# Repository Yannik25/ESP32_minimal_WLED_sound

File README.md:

# ESP32_minimal_WLED_sound

 Either install WLED and configure Digital LEDs on GPIO 2 and 4 with following functions:
 - 2 channels for Digital LEDs
 - 1 mosfet switch output
 - sound reactive with microphone
 
 or install ESPHome to have full support of following:
 - 2 channels for Digital LEDs
 - 1 mosfet switch output
 - INA226 current sensing

# ESPHome ESP32 Sound Module WebInstaller

ESPHome Configuration:

It includes a GitHub workflow that will automatically build the configuration(s) and then deploys a simple 
website via GitHub pages that utilises [ESP Web Tools](https://esphome.github.io/esp-web-tools/) for users to 
easily install your project onto their device.

## Instructions
Open: [https://yannik25.github.io/ESP32_minimal_WLED_sound/](https://yannik25.github.io/ESP32_minimal_WLED_sound/) and follow instructions.

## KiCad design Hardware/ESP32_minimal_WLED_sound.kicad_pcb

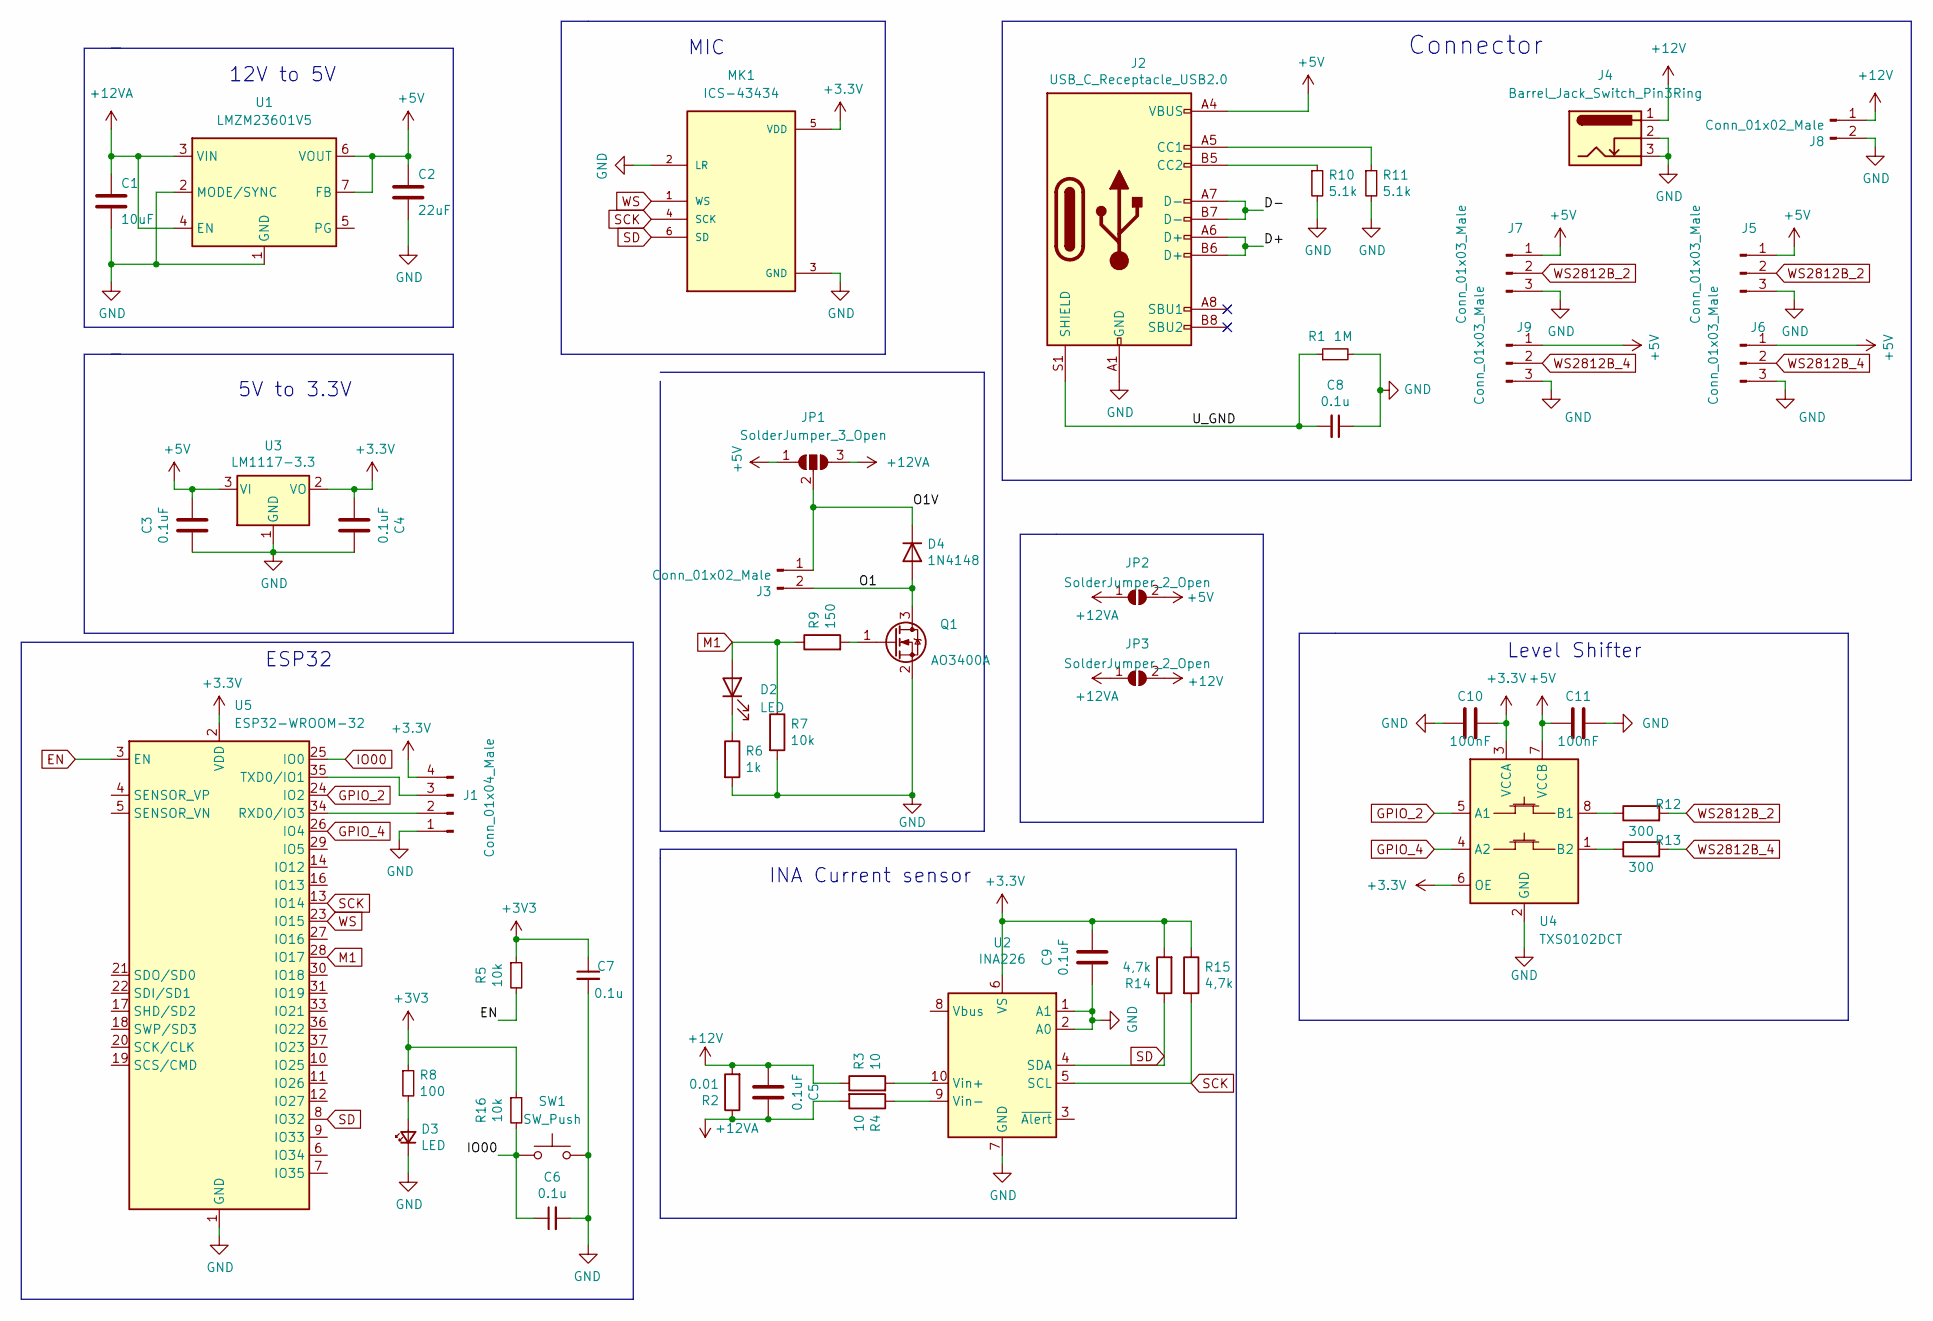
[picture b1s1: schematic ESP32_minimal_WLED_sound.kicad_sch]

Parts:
C1: 10uF; C_0603_1608Metric
C2: 22uF; C_0805_2012Metric
C3, C4, C9: 0.1uF; C_0805_2012Metric
C5: 0.1uF; C_0603_1608Metric
C6, C7, C8: 0.1u; C_0603_1608Metric; LCSC C14663
C10, C11: 100nF; C_0603_1608Metric
D2: LED; LED_0603_1608Metric
D3: LED; LED_0603_1608Metric; LCSC C205445
D4: 1N4148; D_1206_3216Metric
J1: Conn_01x04_Male; PinHeader_1x04_P2.54mm_Vertical
J2: USB_C_Receptacle_USB2.0; USB_C_Receptacle_HRO_TYPE-C-31-M-12; LCSC C165948
J3, J8: Conn_01x02_Male; TerminalBlock_Phoenix_MKDS-1,5-2-5.08_1x02_P5.08mm_Horizont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
J4: Barrel_Jack_Switch_Pin3Ring; BarrelJack_GCT_DCJ200-10-A_Horizontal
J5, J6: Conn_01x03_Male; JST_EH_B3B-EH-A_1x03_P2.50mm_Vertical
J7, J9: Conn_01x03_Male; PinHeader_1x03_P2.54mm_Vertical
JP1: SolderJumper_3_Open; SolderJumper-3_P1.3mm_Open_Pad1.0x1.5mm
JP2, JP3: SolderJumper_2_Open; SolderJumper-2_P1.3mm_Open_Pad1.0x1.5mm
MK1: ICS-43434; MIC_ICS-43434
Q1: AO3400A; SOT-23
R1: 1M; R_0603_1608Metric; LCSC C163928
R2: 0.01; R_0805_2012Metric
R3, R4: 10; R_0603_1608Metric
R5, R16: 10k; R_0603_1608Metric; LCSC C99198
R6: 1k; R_0603_1608Metric
R7: 10k; R_0603_1608Metric
R8: 100; R_0603_1608Metric; LCSC C22775
R9: 150; R_0603_1608Metric
R10, R11: 5.1k; R_0603_1608Metric; LCSC C163928
R12, R13: 300; R_0603_1608Metric
R14, R15: 4,7k; R_0603_1608Metric
SW1: SW_Push; SW_Push_SPST_NO_Alps_SKRK
U1: LMZM23601V5; Texas_SIL0010A_MicroSiP-10-1EP_3.8x3mm_P0.6mm_EP0.7x2.9mm_T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
U2: INA226; VSSOP-10_3x3mm_P0.5mm
U3: LM1117-3.3; SOT-223
U4: TXS0102DCT; SSOP-8_2.95x2.8mm_P0.65mm
U5: ESP32-WROOM-32

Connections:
+5V: C2.1, C3.1, C11.1, J2.A4 (VBUS), J2.A9 (VBUS), J2.B4 (VBUS), J2.B9 (VBUS), J5.1, J6.1, J7.1, J9.1, JP1.1 (A), JP2.2 (B), U1.6 (VOUT), U1.7 (FB), U3.3 (VI), U4.7 (VCCB)
+12V: C5.2, J4.1, J8.1, JP3.2 (B), R2.2, R3.1
+12VA: C1.1, C5.1, JP1.3 (B), JP2.1 (A), JP3.1 (A), R2.1, R4.2, U1.3 (VIN), U1.4 (EN)
/D+: J2.A6 (D+), J2.B6 (D+)
/D-: J2.A7 (D-), J2.B7 (D-)
/O1: D4.2 (A), J3.2, Q1.3 (D)
/O1V: D4.1 (K), J3.1, JP1.2 (C)
/U_GND: C8.2, J2.S1 (SHIELD), R1.1
EN: R5.2, U5.3 (EN)
GND: C1.2, C2.2, C3.2, C4.1, C6.2, C7.2, C8.1, C9.2, C10.1, C11.2, D3.1 (K), J1.1, J2.A1 (GND), J2.A12 (GND), J2.B1 (GND), J2.B12 (GND), J4.2, J4.3, J5.3, J6.3, J7.3, J8.2, J9.3, MK1.2 (LR), MK1.3 (GND), Q1.2 (S), R1.2, R6.2, R7.2, R10.2, R11.2, SW1.2, U1.1 (GND), U1.2 (MODE/SYNC), U1.11 (GND), U2.1 (A1), U2.2 (A0), U2.7 (GND), U3.1 (GND), U4.2 (GND), U5.1 (GND), U5.15 (GND), U5.38 (GND), U5.39 (GND)
GPIO_2: U4.5 (A1), U5.24 (IO2)
GPIO_4: U4.4 (A2), U5.26 (IO4)
IO00: C6.1, R16.2, SW1.1, U5.25 (IO0)
M1: D2.2 (A), R7.1, R9.1, U5.28 (IO17)
unnamed: D2.1 (K), R6.1
unnamed: D3.2 (A), R8.2
unnamed: J1.2, U5.34 (RXD0/IO3)
unnamed: J1.3, U5.35 (TXD0/IO1)
unnamed: J2.A5 (CC1), R11.1
unnamed: J2.B5 (CC2), R10.1
unnamed: Q1.1 (G), R9.2
unnamed: R3.2, U2.10 (Vin+)
unnamed: R4.1, U2.9 (Vin-)
unnamed: R12.1, U4.8 (B1)
unnamed: R13.1, U4.1 (B2)
SCK: MK1.4 (SCK), R15.2, U2.5 (SCL), U5.13 (IO14)
SD: MK1.6 (SD), R14.1, U2.4 (SDA), U5.8 (IO32)
WS: MK1.1 (WS), U5.23 (IO15)
WS2812B_2: J5.2, J7.2, R12.2
WS2812B_4: J6.2, J9.2, R13.2

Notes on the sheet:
MIC
Level Shifter
ESP32
Connector
12V to 5V
5V to 3.3V
INA Current sensor

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
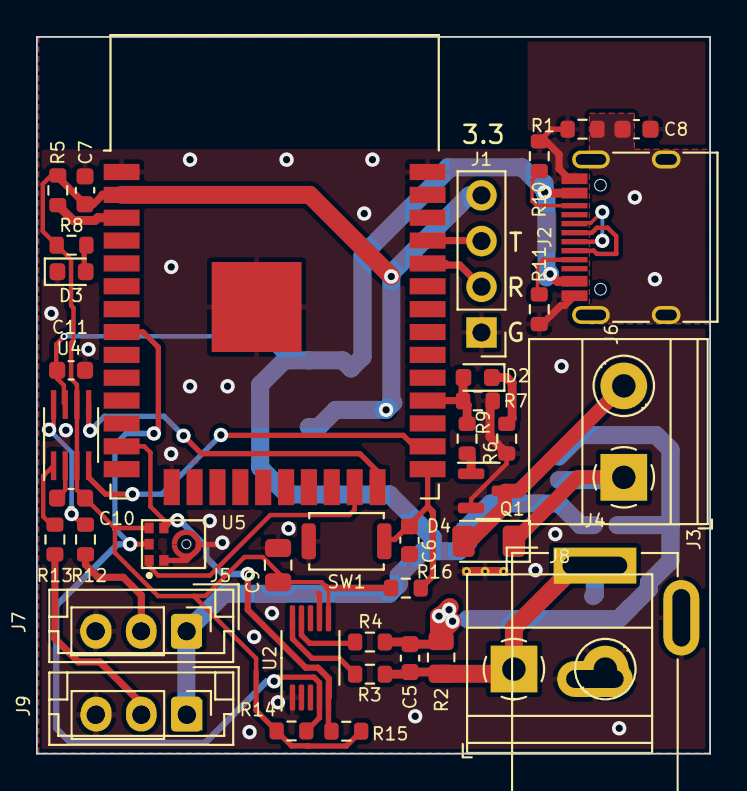
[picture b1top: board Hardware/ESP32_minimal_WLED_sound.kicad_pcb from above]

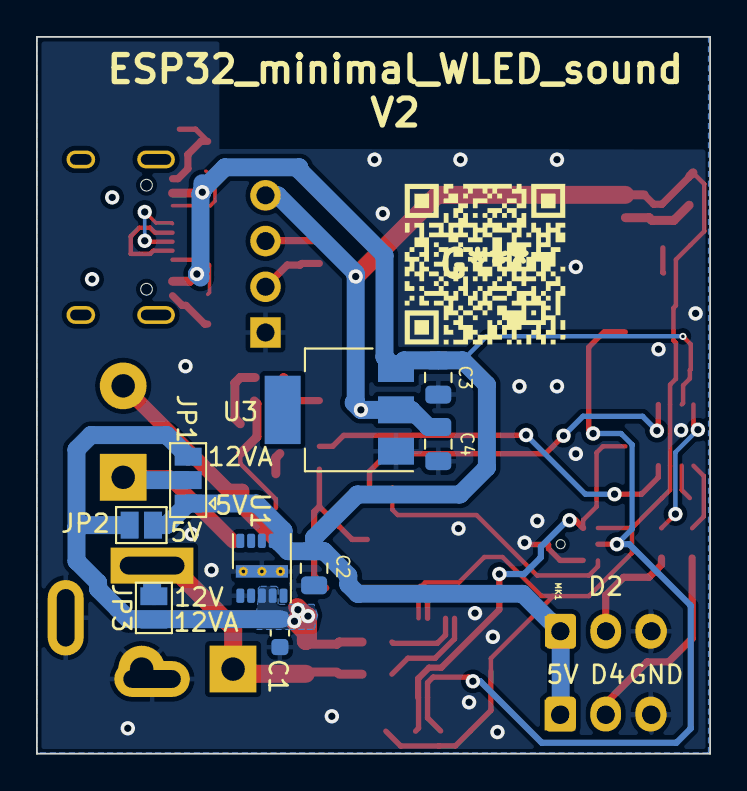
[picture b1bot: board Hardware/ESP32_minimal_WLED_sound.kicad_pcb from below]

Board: 2 copper layers, 37.4 x 39.8 mm, 50 parts (9 on the bottom side), 31 nets.

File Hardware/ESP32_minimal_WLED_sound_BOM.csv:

Comment,Designator,Footprint,LCSC
100nF,C1 C2 C3 C4 C9,Capacitor_SMD:C_0805_2012Metric,
100nF,C5 C6 C7 C8 C10 C11,Capacitor_SMD:C_0603_1608Metric,
LED,D2 D3,LED_SMD:LED_0603_1608Metric,
1N4148,D4,Diode_SMD:D_1206_3216Metric,
USB_C_Receptacle_USB2.0,J2,Connector_USB:USB_C_Receptacle_HRO_TYPE-C-31-M-12,C165948
ICS-43434,MK1,ICS-43434:MIC_ICS-43434,
AO3400A,Q1,Package_TO_SOT_SMD:SOT-23,
1M,R1,Resistor_SMD:R_0603_1608Metric,C163928
5.1k,R10 R11,Resistor_SMD:R_0603_1608Metric,C163928
300,R12 R13,Resistor_SMD:R_0603_1608Metric,
4,7k,R14 R15,Resistor_SMD:R_0603_1608Metric,
0.01,R2,Resistor_SMD:R_0805_2012Metric,
10,R3 R4,Resistor_SMD:R_0603_1608Metric,
10k,R5 R7,Resistor_SMD:R_0603_1608Metric,C99198
1k,R6,Resistor_SMD:R_0603_1608Metric,
100,R8,Resistor_SMD:R_0603_1608Metric,C22775
150,R9,Resistor_SMD:R_0603_1608Metric,
Boot,SW2,Button_Switch_SMD:SW_SPST_B3U-1000P-B,C115357
LM1117-5,U1,Package_TO_SOT_SMD:SOT-223,
INA226,U2,Package_SO:VSSOP-10_3x3mm_P0.5mm,
LM1117-3.3,U3,Package_TO_SOT_SMD:SOT-223,
TXS0102DCT,U4,Package_SO:SSOP-8_2.95x2.8mm_P0.65mm,
ESP32-WROOM-32,U5,RF_Module:ESP32-WROOM-32,

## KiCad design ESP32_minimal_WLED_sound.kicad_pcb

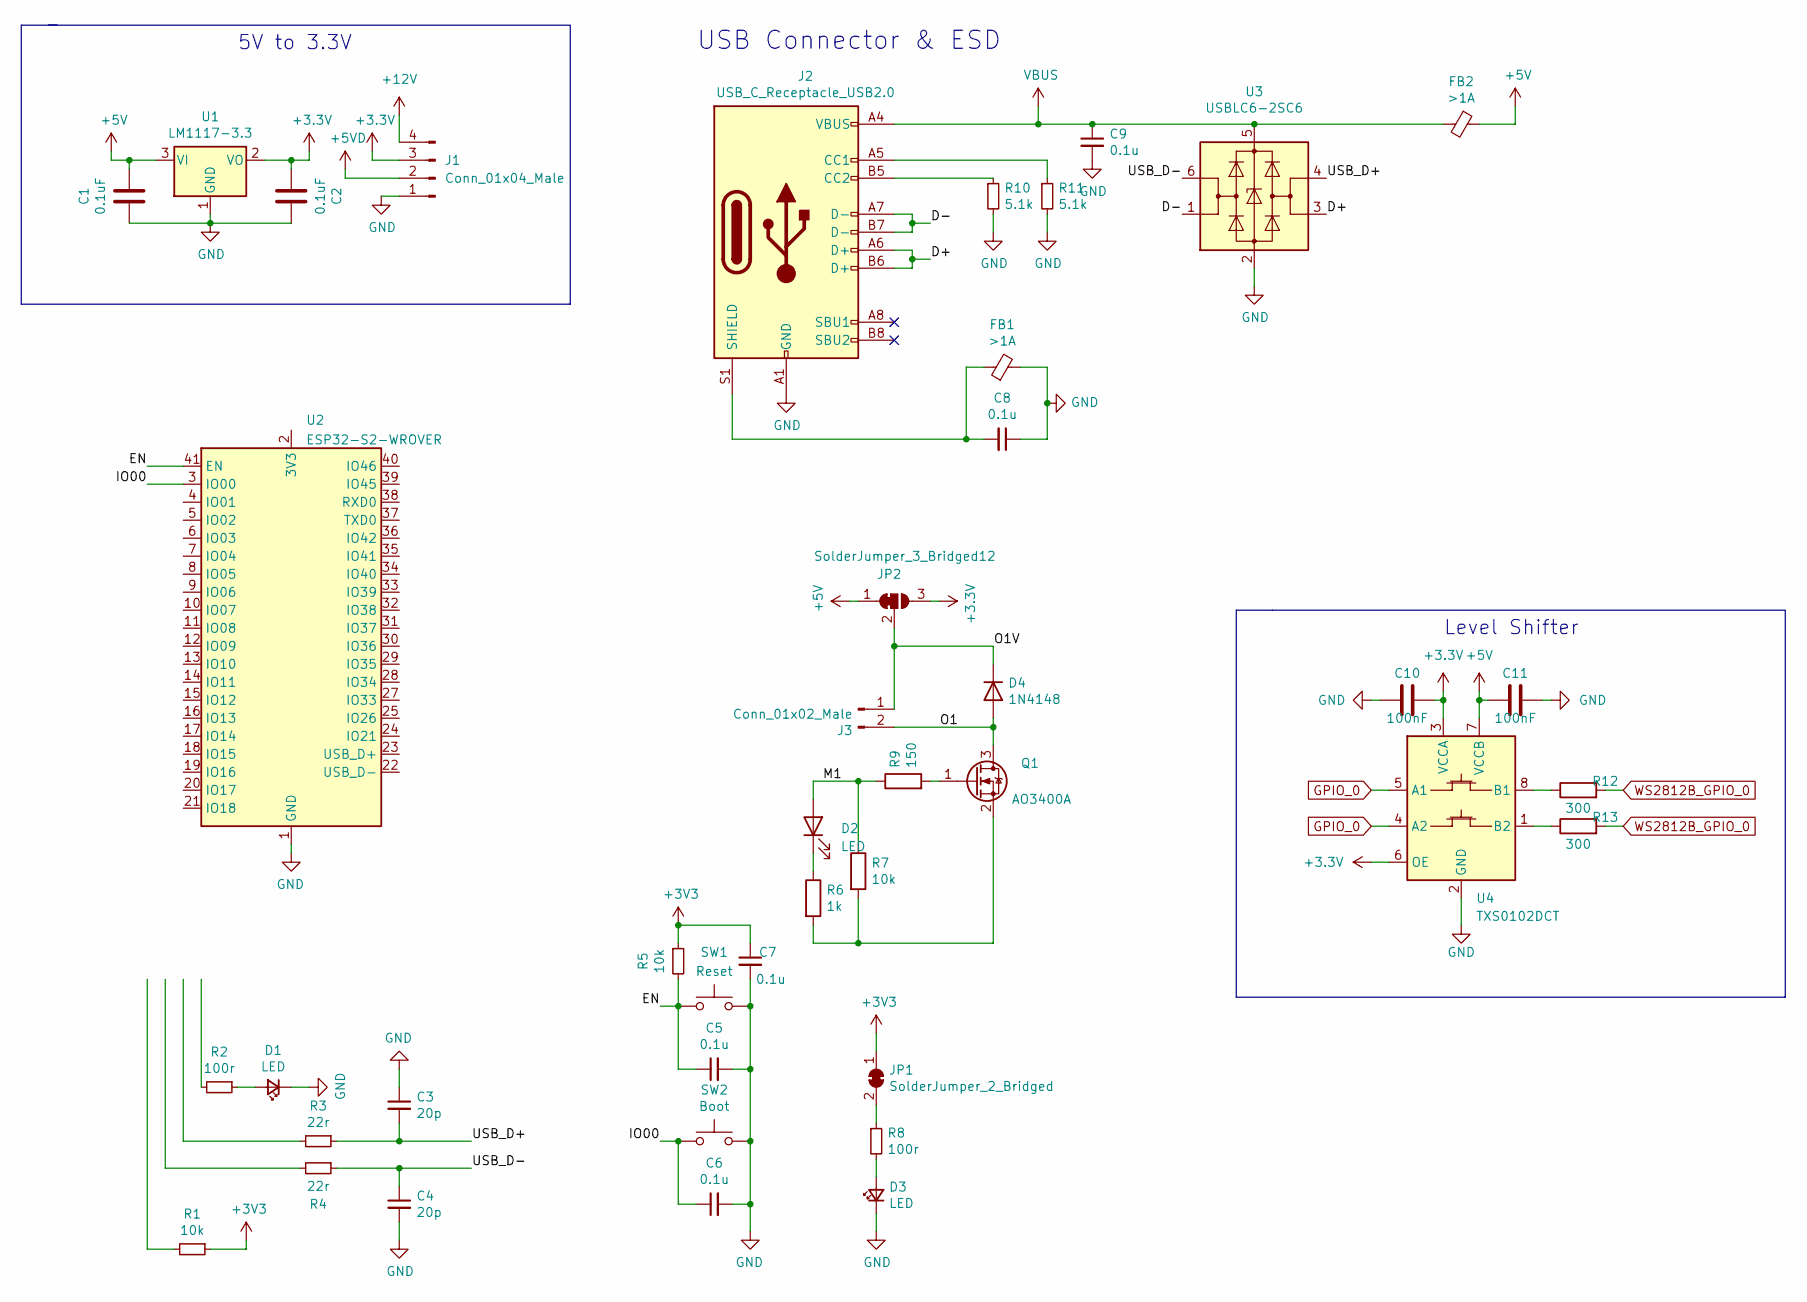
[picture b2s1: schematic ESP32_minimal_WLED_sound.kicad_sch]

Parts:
C1, C2: 0.1uF; C_0805_2012Metric
C3, C4: 20p; C_0603_1608Metric; LCSC C1648
C5, C6, C7, C8, C9: 0.1u; C_0603_1608Metric; LCSC C14663
C10, C11: 100nF; C_0603_1608Metric_Pad1.08x0.95mm_HandSolder
D1: LED; LED_0603_1608Metric; LCSC C205443
D2: LED; LED_0603_1608Metric
D3: LED; LED_0603_1608Metric; LCSC C205445
D4: 1N4148; D_1206_3216Metric
FB1, FB2: >1A; L_0603_1608Metric; LCSC C24821
J1: Conn_01x04_Male; PinHeader_1x04_P2.54mm_Horizontal
J2: USB_C_Receptacle_USB2.0; USB_C_Receptacle_HRO_TYPE-C-31-M-12; LCSC C165948
J3: Conn_01x02_Male; PhoenixContact_MSTBA_2,5_2-G-5,08_1x02_P5.08mm_Horizontal
JP1: SolderJumper_2_Bridged; SolderJumper-2_P1.3mm_Bridged_RoundedPad1.0x1.5mm
JP2: SolderJumper_3_Bridged12; SolderJumper-3_P1.3mm_Bridged12_Pad1.0x1.5mm
Q1: AO3400A; SOT-23
R1, R5: 10k; R_0603_1608Metric; LCSC C99198
R2, R8: 100r; R_0603_1608Metric; LCSC C22775
R3, R4: 22r; R_0603_1608Metric; LCSC C23345
R6: 1k; R_0805_2012Metric
R7: 10k; R_0805_2012Metric
R9: 150; R_0805_2012Metric
R10, R11: 5.1k; R_0603_1608Metric; LCSC C163928
R12, R13: 300; C_0603_1608Metric_Pad1.08x0.95mm_HandSolder
SW1: Reset; Alps_SKRK; LCSC C115357
SW2: Boot; Alps_SKRK; LCSC C115357
U1: LM1117-3.3; SOT-223
U2: ESP32-S2-WROVER
U3: USBLC6-2SC6; SOT-23-6; LCSC C7519
U4: TXS0102DCT; SSOP-8_2.95x2.8mm_P0.65mm

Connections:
+5V: C1.1, C11.1, FB2.1, JP2.1 (A), U1.3 (VI), U4.7 (VCCB)
+5VD: J1.2
+12V: J1.4
/D+: J2.A6 (D+), J2.B6 (D+), U3.3 (I/O2)
/D-: J2.A7 (D-), J2.B7 (D-), U3.1 (I/O1)
/EN: C5.1, R5.2, SW1.2, U2.41 (EN)
/IO00: C6.1, SW2.2, U2.3 (IO00)
/M1: D2.2 (A), R7.1, R9.1
/O1: D4.2 (A), J3.2, Q1.3 (D)
/O1V: D4.1 (K), J3.1, JP2.2 (C)
/USB_D+: C3.2, R3.1, U3.4 (I/O2)
/USB_D-: C4.1, R4.1, U3.6 (I/O1)
GND: C1.2, C2.1, C3.1, C4.2, C5.2, C6.2, C7.2, C8.1, C9.2, C10.1, C11.2, D1.1 (K), D3.1 (K), FB1.2, J1.1, J2.A1 (GND), J2.A12 (GND), J2.B1 (GND), J2.B12 (GND), R10.2, R11.2, SW1.1, SW2.1, U1.1 (GND), U2.1 (GND), U2.26 (GND), U2.42 (GND), U2.43 (GND), U3.2 (GND), U4.2 (GND)
GPIO_0: U4.4 (A2), U4.5 (A1)
unnamed: C8.2, FB1.1, J2.S1 (SHIELD)
unnamed: D1.2 (A), R2.1
unnamed: D2.1 (K), R6.1
unnamed: D3.2 (A), R8.2
unnamed: J2.A5 (CC1), R11.1
unnamed: J2.B5 (CC2), R10.1
unnamed: JP1.2 (B), R8.1
unnamed: Q1.1 (G), R9.2
unnamed: Q1.2 (S), R6.2, R7.2
unnamed: R12.1, U4.8 (B1)
unnamed: R13.1, U4.1 (B2)
VBUS: C9.1, FB2.2, J2.A4 (VBUS), J2.A9 (VBUS), J2.B4 (VBUS), J2.B9 (VBUS), U3.5 (VBUS)
WS2812B_GPIO_0: R12.2, R13.2

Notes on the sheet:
Level Shifter
USB Connector & ESD
5V to 3.3V

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
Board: 2 copper layers, 39 parts (0 on the bottom side), 22 nets, no tracks yet.

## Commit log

2022-02-03 move files
2022-02-04 update to V1
2022-02-04 add bom and position files
2022-02-04 fix top position file
2022-03-02 fix esp32 EN and IO0, Todo: solder jumper and 12V to 5V
2022-03-02 add image and esphome configuration
2022-03-02 remove files from branch
2022-03-02 Deploying to gh-pages from @ Yannik25/ESP32_minimal_WLED_sound@30e2d9974a135df2e51421dbeafc83d27c7121a0 🚀
2022-03-02 update esphome config
2022-03-02 fix config
2022-03-02 Deploying to gh-pages from @ Yannik25/ESP32_minimal_WLED_sound@6475db436bcb137824a3382ed12547e04d441da3 🚀
2022-03-02 Deploying to gh-pages from @ Yannik25/ESP32_minimal_WLED_sound@06c1a0d026d32610e9b16ccdd4e8f791dfcf7a7f 🚀
2022-05-09 switch 12V to 5V to DCDC
2022-05-09 Deploying to gh-pages from @ Yannik25/ESP32_minimal_WLED_sound@5c54eacaa8fef9173f75d03f88d542b596195ac1 🚀
2022-05-13 update button
2022-05-13 Deploying to gh-pages from @ Yannik25/ESP32_minimal_WLED_sound@8fe919248926d3c7068b8933a6ec565e170f280f 🚀
